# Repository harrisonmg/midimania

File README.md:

# A Custom MIDI Controller Design

## Mechanical
* Designed in [Onshape Free](https://www.onshape.com/en/products/free)
* 8 beatmania IIDX clone switches w/ LEDs from AliExpress
* 4 rotary potentiometers and 4 slide potentiometers
* Faceplate laser cut on 1/8" 5052 aluminum by [SendCutSend](https://sendcutsend.com/)
* Using aluminum wall mount sign holders with rubber pads as legs

## Electrical
* Based around a [Teensy 3.2](https://www.pjrc.com/store/teensy32.html) because I had one
* Connected via PCB and 18 gauge copper jewelry wire
* Switches wired inline with LEDs to light up when pressed
* PCB designed in [KiCad](https://www.kicad.org/)
* PCB manufactured by [Oshpark](https://oshpark.com/)
* NGE artwork desgined in [Inkscape](https://inkscape.org/)
* Art converted to footprints with [svg2mod](https://github.com/svg2mod/svg2mod)
* Special thanks to [Uri Shaked's Practical Guide to Designing PCB Art](https://blog.wokwi.com/a-practical-guide-to-designing-pcb-art/)

## Software
* Running Arduino
* Using [USB MIDI](https://www.pjrc.com/teensy/td_midi.html#:~:text=When%20you%20select%20%22MIDI%22%20from,3.0%20to%203.6%20are%20supported.)

## Bill of Materials
|Part|Price|
|---|---|
|[PCB](https://oshpark.com/)|$51.65|
|[Laser Cut Aluminum Faceplate](https://sendcutsend.com/)|$39.15|
|[Switch (8x)](https://www.aliexpress.com/item/2251832160522560.html?spm=a2g0o.order_detail.0.0.443df19cTFTVqb&gatewayAdapt=4itemAdapt)|$24.99|
|[Teensy 3.2](https://www.pjrc.com/store/teensy32.html)|$19.80|
|[Aluminum Legs (10x)](https://www.amazon.com/gp/product/B07R1SLTY6/ref=ppx_yo_dt_b_search_asin_title?ie=UTF8&psc=1)|$13.99|
|[Jewlery Wire (55ft)](https://www.amazon.com/gp/product/B086VH27KM/ref=ppx_yo_dt_b_search_asin_title?ie=UTF8&th=1)|$12.99|
|[Slide Potentiometer Screws (10x)](https://www.mcmaster.com/97763A407/)|$8.67|
|[Rotary Potentiometer](https://www.adafruit.com/product/5280)|$7.80 ($1.95 ea)|
|[Slide Potentiometer](https://www.adafruit.com/product/4272)|$7.80 ($1.95 ea)|
|[Rubber Foot Pads (50x)](https://www.amazon.com/dp/B01LDLJF5K?psc=1&ref=ppx_yo2ov_dt_b_product_details)|$7.79|
|[1k Through-hole Resistor (100x)](https://www.amazon.com/dp/B07HDDWFDD?ref=ppx_yo2ov_dt_b_product_details&th=1)|$4.99|
|[Potentiometer Knobs (20x)](https://www.ebay.com/itm/192481232352)|$4.73|
|[Slide Potentiometer Knobs (10x)](https://www.ebay.com/itm/384835783660)|$2.45|
|TOTAL|$206.80 (yikes)|

## Build Notes

Everything fit in the plate beautifully. The faceplate only needed a little bit of post-processing with a file and some scotch brite.

The rotary potentiometer pins were longer than expected. I extended each slide potentiometer pin with the metal innard of a female pin header so that the PCB will sit parallel to the faceplate.

The aluminum legs strip easily.

The PCBs look great. There's a few spots where the silkscreen wasn't printed. I knew the fab house would remove silkscreen on top of exposed copper, but it looks like they also remove silkscreen within a small radius around exposed copper. Also, some small lines on the left were left out of my Gerbers; I'm not sure how that happened.

The copper wiring was a pain. Removing the coating from the jewelry wire and trying to keep everything straight and sized correctly was tedious.

The easiest method I found to remove the coating was scraping with a razor blade. Fun-Tak was useful for securing things while soldering.

I could've benefitted from better modeling of the wiring ahead of time, and I should've used through-hole pads on the PCB for the wire.

In the future I might try to use thicker wire that holds it shape better. Since I still have a bunch of wire left over, I'll probably find a way to strip a large amount of it ahead of time. I think I'll also buy better solder.

This sketch I found in my notes is pretty much how each switch is wired.

Finally, the linear and rotary potentiometer knobs both needed some work. I bought rotary pots without knob splines because they seemed nicer (apart from that), so I just drilled out the knobs a big to fit on. The linear pots came with knobs, but I bought nicer ones that were way too tight. I shaved down the linear pot stems a bit with a razor blade and used some Fun-Tak to try and help them sit a bit higher and not scratch against the plate.

Both sets of knobs still rub on the plate a bit, I think 1/8" is probably the upper limit these parts are intended to be mounted through.

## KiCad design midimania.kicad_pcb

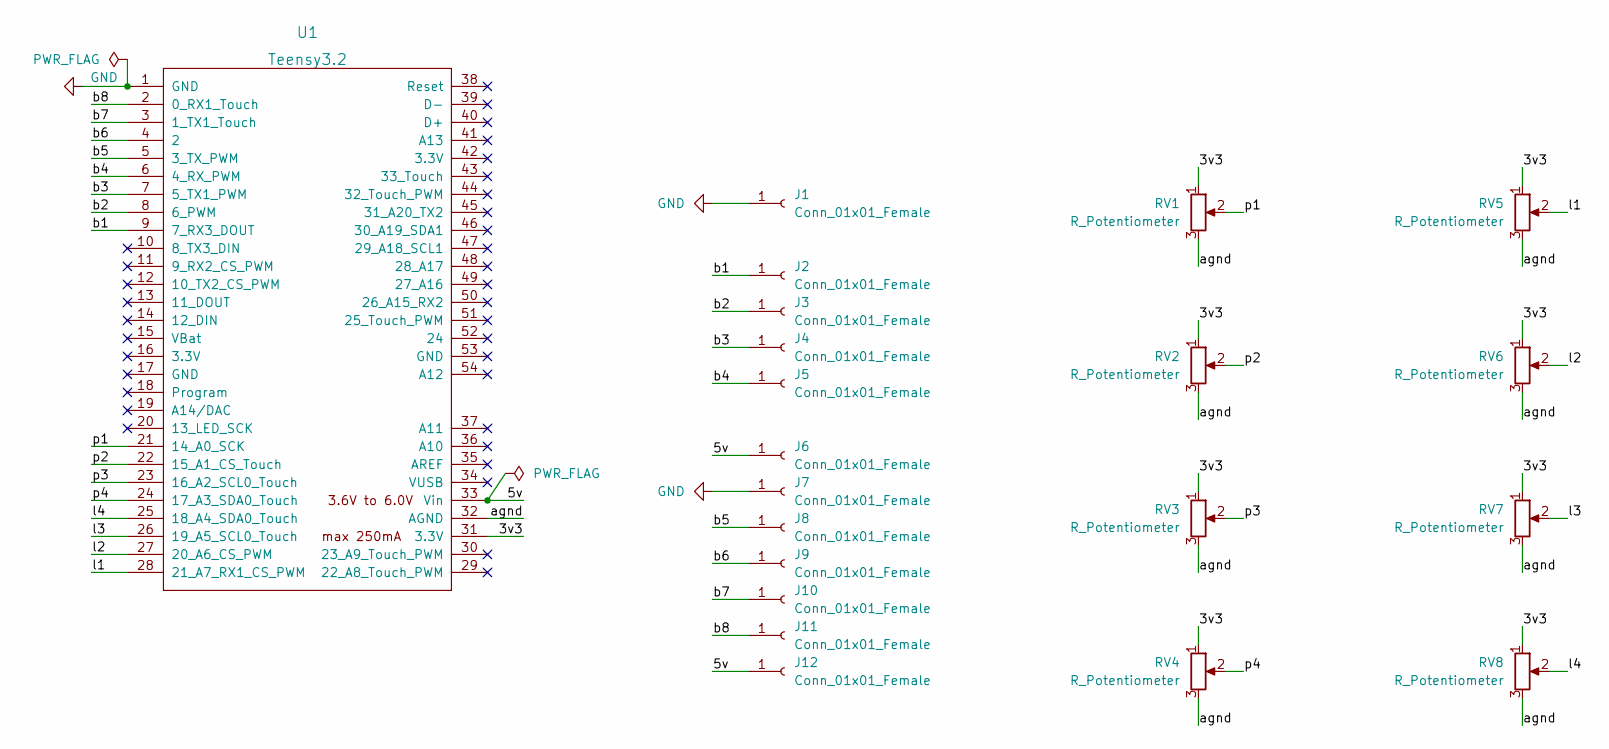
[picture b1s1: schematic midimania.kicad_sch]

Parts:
J1, J2, J3, J4, J5, J6, J7, J8, J9, J10, J11, J12: Conn_01x01_Female; TestPoint_Pad_1.5x1.5mm
RV1, RV2, RV3, RV4: R_Potentiometer; Potentiometer_Alpha_RV16AF-41
RV5, RV6, RV7, RV8: R_Potentiometer; Potentiometer_Slide_C3031N
U1: Teensy3.2; Teensy30_31_32_LC

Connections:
/3v3: RV1.1, RV2.1, RV3.1, RV4.1, RV5.1, RV6.1, RV7.1, RV8.1, U1.31 (3.3V)
/5v: J6.1, J12.1, U1.33 (Vin)
/agnd: RV1.3, RV2.3, RV3.3, RV4.3, RV5.3, RV6.3, RV7.3, RV8.3, U1.32 (AGND)
/b1: J2.1, U1.9 (7_RX3_DOUT)
/b2: J3.1, U1.8 (6_PWM)
/b3: J4.1, U1.7 (5_TX1_PWM)
/b4: J5.1, U1.6 (4_RX_PWM)
/b5: J8.1, U1.5 (3_TX_PWM)
/b6: J9.1, U1.4 (2)
/b7: J10.1, U1.3 (1_TX1_Touch)
/b8: J11.1, U1.2 (0_RX1_Touch)
/l1: RV5.2, U1.28 (21_A7_RX1_CS_PWM)
/l2: RV6.2, U1.27 (20_A6_CS_PWM)
/l3: RV7.2, U1.26 (19_A5_SCL0_Touch)
/l4: RV8.2, U1.25 (18_A4_SDA0_Touch)
/p1: RV1.2, U1.21 (14_A0_SCK)
/p2: RV2.2, U1.22 (15_A1_CS_Touch)
/p3: RV3.2, U1.23 (16_A2_SCL0_Touch)
/p4: RV4.2, U1.24 (17_A3_SDA0_Touch)
GND: J1.1, J7.1, U1.1 (GND)

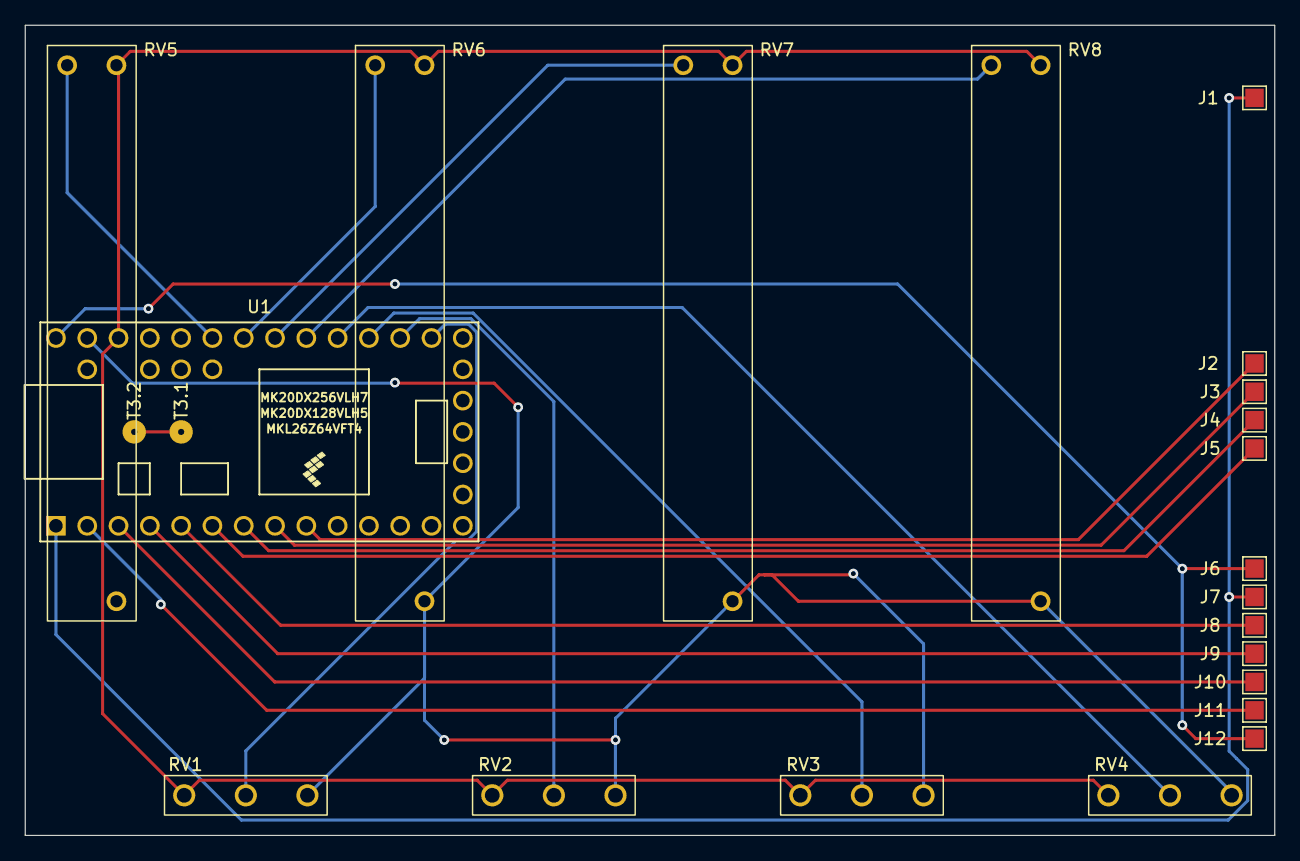
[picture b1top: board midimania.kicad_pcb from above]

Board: 2 copper layers, 101.4 x 65.8 mm, 21 parts (0 on the bottom side), 20 nets.

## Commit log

2022-06-14 pcb design
2022-06-14 added faceplate and README
2022-06-16 updated BOM
2022-06-17 updated build notes
2022-06-17 added prelim ino
2022-06-27 finished code
2022-07-12 updated fader zero
